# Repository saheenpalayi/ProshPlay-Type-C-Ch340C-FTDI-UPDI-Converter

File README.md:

# ProshPlay-Type-C-Ch340C-FTDI-UPDI-Converter

## PCB Layout

## 3D Output

## BOM

| Id | Designator | Footprint | Quantity | Designation | Supplier and ref |
| --- | --- | --- | --- | --- | --- |
| 1 | J2 | PinSocket_1x06_P2.54mm_Horizontal_SMD | 1 | 1x06 Pin header 2.54 SMD |  |
| 2 | C1 | C_1206 | 1 | 100nF |  |
| 3 | C2 | C_1206 | 1 | 10nF |  |
| 4 | R3 | R_1206 | 1 | 1K |  |
| 5 | R1,R2 | R_1206 | 2 | 1k |  |
| 6 | SW2 | SW_JS202011SCQN | 1 | SW_Slide_DPDT |  |
| 7 | D5 | Diode_Schottky_MiniSMA | 1 | 1N5817 / shotkey 100mA |  |
| 8 | J1 | ProshPlay-Type-C-breakout-board | 1 | USB_Type-C_Breakout |  |
| 9 | U2 | SOT-23-3 | 1 | 3.3 v LDO 100mA |  |
| 10 | D1 | LED_1206 | 1 | RED |  |
| 11 | D3 | SOD-123T | 1 | 1A Schottky |  |
| 12 | SW1 | Switch_Slide_RightAngle_CnK_AYZ0102AGRLC_7.2x3mm | 1 | Switch_Slide_RightAngle_CnK |  |
| 13 | C4,C3 | C_1206 | 2 | 1uF |  |
| 14 | JP1 | Jumper_1206 | 1 | 0ohm |  |
| 15 | D4 | LED_1206 | 1 | GREEN |  |
| 16 | R4 | R_1206 | 1 | 499 Ohm |  |
| 17 | U1 | SOIC-16_3.9x9.9mm_P1.27mm | 1 | CH340C |  |
| 18 | D2 | LED_1206 | 1 | BLUE |  |

## Downloads
- [Schematic.pdf](<Design Files/FTDI-UPDI-CH340-Type-c.pdf>)
- [gerber.zip](<Gerber Files/gerber.zip>)

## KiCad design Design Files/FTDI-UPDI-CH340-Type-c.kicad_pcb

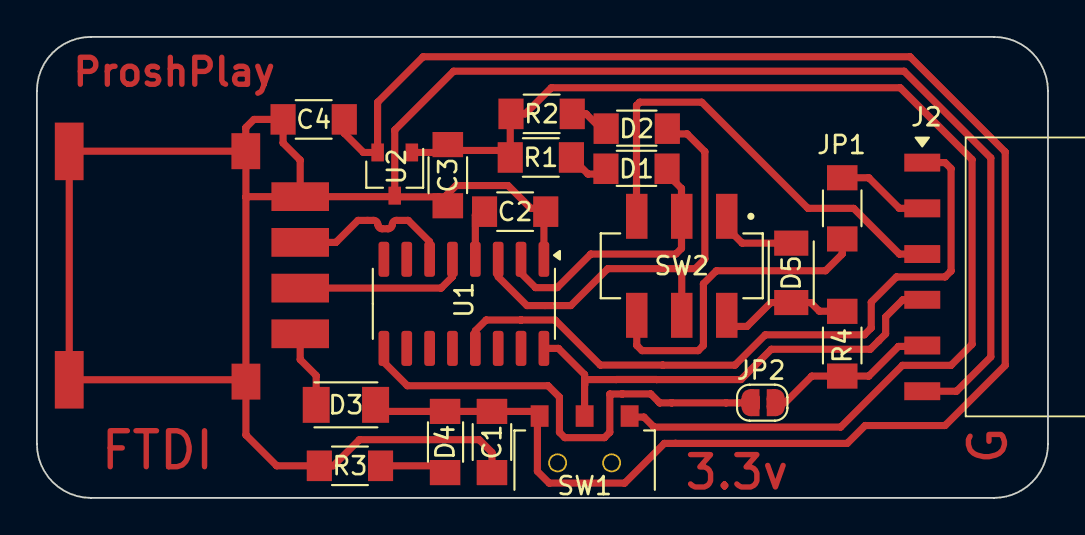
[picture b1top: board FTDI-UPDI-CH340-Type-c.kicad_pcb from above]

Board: 2 copper layers, 56.2 x 25.6 mm, 21 parts (0 on the bottom side), 21 nets.

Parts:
C1, C3, C4: 100nF; C_1206
C2: 10nF; C_1206
D1: Yellow; LED_1206
D2: Green; LED_1206
D3: Diode_Schottky_MiniSMA; SOD-123T
D4: RED; LED_1206
D5: Diode_Schottky_MiniSMA
J1: USB_Type-C_Breakout; ProshPlay-Type-C-breakout-board
J2: Conn_PinSocket_FTDI_1x06_P2.54mm_Horizontal_SMD; PinSocket_1x06_P2.54mm_Horizontal_SMD
JP1: Jumper_1206
JP2: SolderJumper_2_Open; SolderJumper-2_P1.3mm_Open_RoundedPad1.0x1.5mm
R1, R2: 1k; R_1206
R3: R_1206
R4: 499 Ohm; R_1206
SW1: Switch_Slide_RightAngle_CnK; Switch_Slide_RightAngle_CnK_AYZ0102AGRLC_7.2x3mm
SW2: SW_Slide_DPDT; SW_JS202011SCQN
U1: CH340C; SOIC-16_3.9x9.9mm_P1.27mm
U2: Regulator_Linear_3.3V_100mA_TexasInstruments; SOT-23-3

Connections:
+3V3: C3.1, R1.1, R2.1, SW1.3 (C), U2.1 (VO)
+5V: C1.1, C4.1, D3.1 (K), D4.2 (A), SW1.1 (A), U2.2 (VI)
CTS: JP2.1 (A), U1.9 (~CTS)
D+: J1.2 (D+), U1.5 (UD+)
D-: J1.3 (D-), U1.6 (UD-)
DTR: J2.1, U1.13 (~DTR)
GND: C1.2, C2.2, C3.2, C4.2, J1.4 (GND), J1.5 (Shield), J2.6, R3.2, U1.1 (GND), U2.3 (GND)
unnamed: D1.2 (A), R1.2
unnamed: D2.2 (A), R2.2
unnamed: D4.1 (K), R3.1
unnamed: D5.2 (A), R4.1, SW2.6 (C)
unnamed: D5.1 (K), SW2.1 (A)
unnamed: J2.2, JP1.2 (B)
unnamed: C2.1, U1.4 (V3)
RX: D2.1 (K), SW2.5 (B), U1.3 (RXD)
T-RX: JP1.1 (A), SW2.4 (A)
T-TX: J2.3, SW2.3 (C)
TX: D1.1 (K), SW2.2 (B), U1.2 (TXD)
UPDI: J2.5, JP2.2 (B), R4.2
VBUS: D3.2 (A), J1.1 (VBUS)
VCC: J2.4, SW1.2 (B), U1.16 (VCC)

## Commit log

2025-04-07 added files
2025-04-07 Added BOM
